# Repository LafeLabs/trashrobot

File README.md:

# trashrobot
trashrobot main web site stuff

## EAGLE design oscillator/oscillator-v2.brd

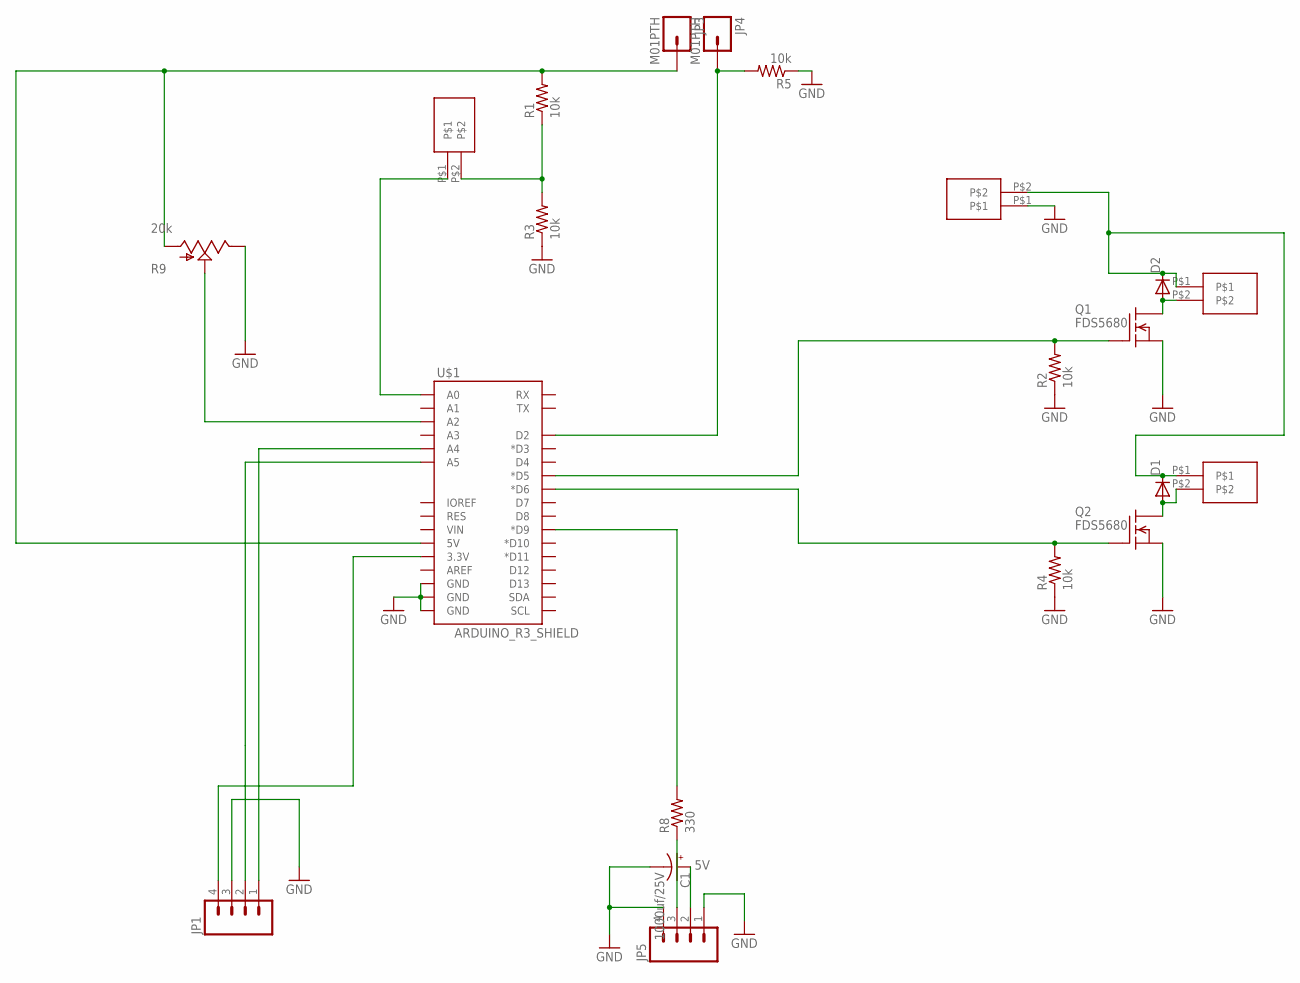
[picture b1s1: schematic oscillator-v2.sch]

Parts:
C1: 1000uf/25V; CPOL-RADIAL-1000UF-25V-KIT
D1, D2: DIODE-DO-214AC; DO-214AC
JP1, JP5: M04PTH; 1X04
JP3, JP4: M01PTH; 1X01
Q1, Q2: FDS5680; SO-8
R1, R2, R3, R4, R5: 10k; R0603
R8: 330; R0603
R9: 20k; ALPS_POT_KIT
U$1: ARDUINO_R3_SHIELD; UNO_R3_SHIELD
U$6: SPRING-TERMINAL
X1, X2, X5: SPRING-TERMINAL

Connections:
5V: C1.+, JP3.1, JP5.2, R1.2, R9.P$3 (A), U$1.5V
BUTTON: JP4.1, R5.2, U$1.D2
CL: JP1.2, U$1.A5
DA: JP1.1, U$1.A4
GND: C1.-, JP1.3, JP5.1, JP5.4, Q1.1 (S), Q1.2 (S), Q1.3 (S), Q2.1 (S), Q2.2 (S), Q2.3 (S), R2.1, R3.1, R4.1, R5.1, R9.P$1 (E), U$1.GND@0 (GND), U$1.GND@1 (GND), U$1.GND@2 (GND), X1.P$1
unnamed: Q1.4 (G), R2.2, U$1.D5 (*D5)
unnamed: R8.2, U$1.D9 (*D9)
unnamed: R1.1, R3.2, X2.P$2
unnamed: D2.A, Q1.5 (D), Q1.6 (D), Q1.7 (D), Q1.8 (D), U$6.P$2
unnamed: D1.A, Q2.5 (D), Q2.6 (D), Q2.7 (D), Q2.8 (D), X5.P$2
unnamed: Q2.4 (G), R4.2, U$1.D6 (*D6)
unnamed: U$1.A0, X2.P$1
unnamed: JP5.3, R8.1
unnamed: R9.P$2 (S), U$1.A2
VCC: JP1.4, U$1.3.3V
VIN: D1.C, D2.C, U$6.P$1, X1.P$2, X5.P$1

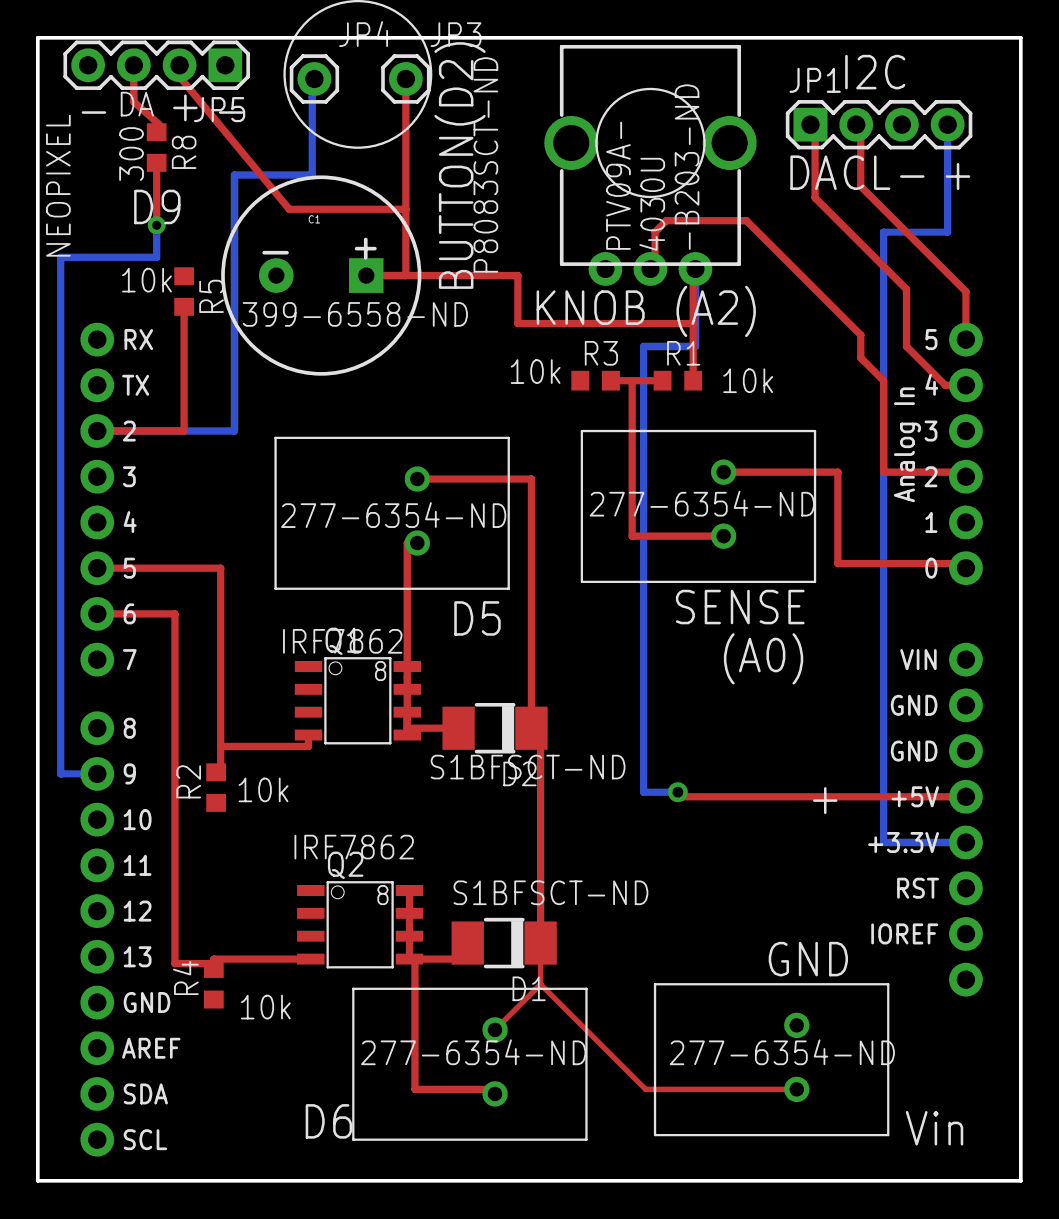
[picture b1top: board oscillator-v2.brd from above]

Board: 2 copper layers, 54.6 x 63.5 mm, 21 parts (0 on the bottom side), 16 nets.

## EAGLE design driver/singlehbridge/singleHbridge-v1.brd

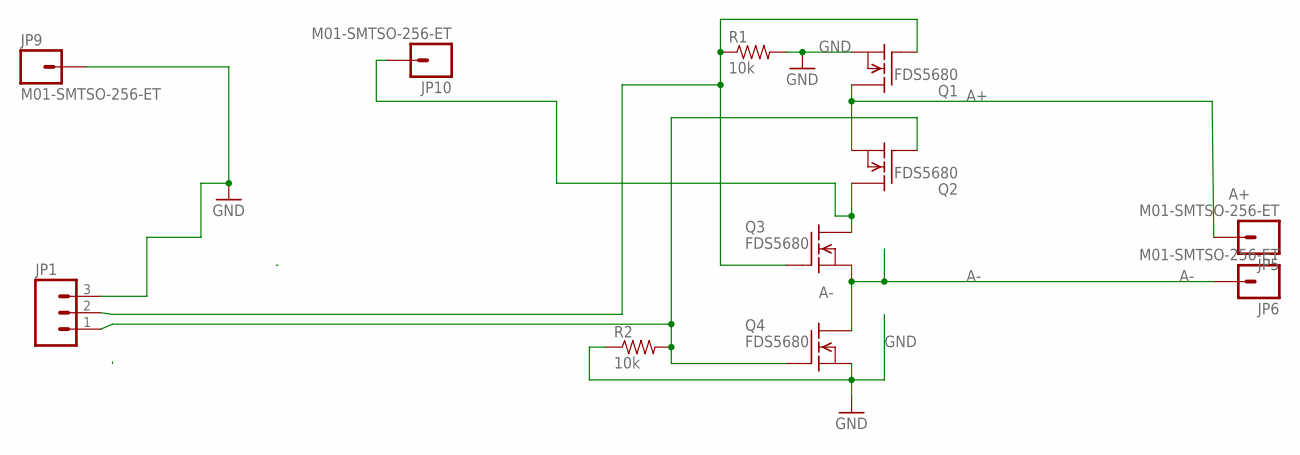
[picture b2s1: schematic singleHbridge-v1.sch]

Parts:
JP1: M03PTH; 1X03
JP5, JP6, JP9, JP10: M01-SMTSO-256-ET; SMTSO-256-ET
Q1, Q2, Q3, Q4: FDS5680; SO-8
R1, R2: 10k; 0603-RES

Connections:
12V: JP10.P$1, Q2.5 (D), Q2.6 (D), Q2.7 (D), Q2.8 (D), Q3.5 (D), Q3.6 (D), Q3.7 (D), Q3.8 (D)
A+: JP5.P$1, Q1.5 (D), Q1.6 (D), Q1.7 (D), Q1.8 (D), Q2.1 (S), Q2.2 (S), Q2.3 (S)
A-: JP6.P$1, Q3.1 (S), Q3.2 (S), Q3.3 (S), Q4.5 (D), Q4.6 (D), Q4.7 (D), Q4.8 (D)
GND: JP1.3, JP9.P$1, Q1.1 (S), Q1.2 (S), Q1.3 (S), Q4.1 (S), Q4.2 (S), Q4.3 (S), R1.2, R2.1
unnamed: JP1.2, Q1.4 (G), Q3.4 (G), R1.1
unnamed: JP1.1, Q2.4 (G), Q4.4 (G), R2.2

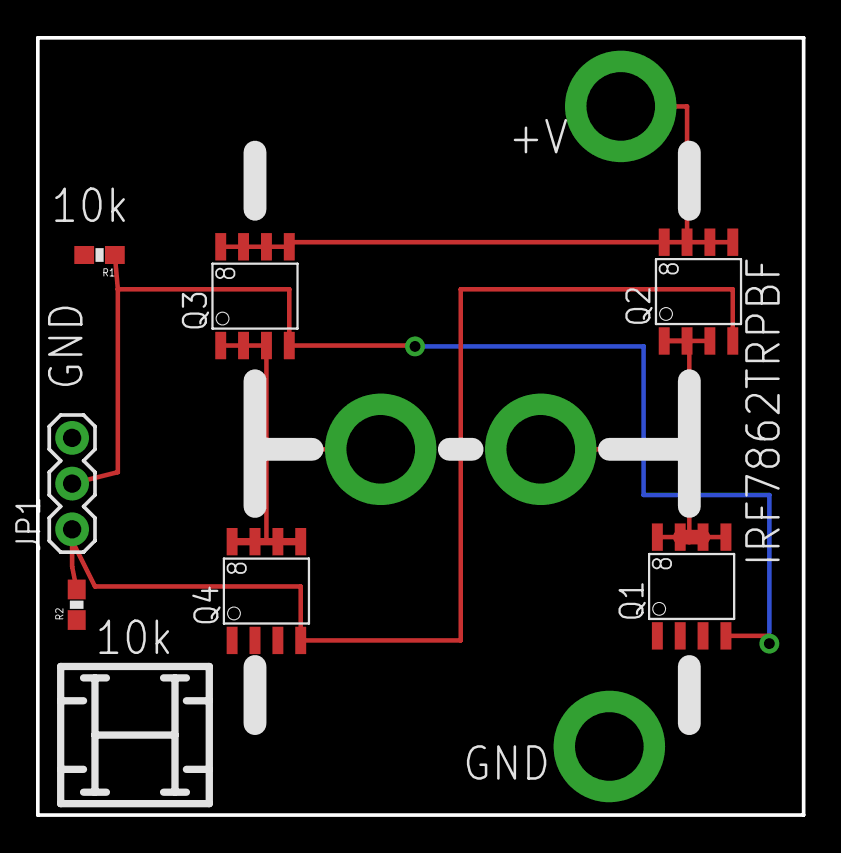
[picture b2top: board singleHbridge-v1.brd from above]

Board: 2 copper layers, 42.5 x 43.2 mm, 11 parts (0 on the bottom side), 6 nets.

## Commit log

2018-01-14 CARDBOARD ROBOT DATA
2018-01-16 trash robots update
2018-01-23 trash robot
2018-02-01 some random circuits or something, who knows
2018-02-04 css based control of arduino which controls robot motors
    I’m not sure why adding a delay was needed to make this work. Perhaps
    something about RC times with 1 megohm bias resistors
2018-02-20 so many things that i have no idea how to summarize. burn Facebook to the ground
2018-04-29 deleted trace to vin

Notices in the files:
oscillator/oscillator-v2.brd:
PUBLIC DOMAIN
NO COPYRIGHTS
parts and their libraries:
SparkFun-Connectors: Licensing: Creative Commons ShareAlike 4.0 International - https://creativecommons.org/licenses/by-sa/4.0
